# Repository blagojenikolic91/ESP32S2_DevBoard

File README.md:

# ESP32-S2-DevelopmentBoard

CUstom DIY Development board based around ESP32-S2, USB typeC, Native USB and fully addressable LED RGB build in. 

Features:

* ESP32-S2
* USB type C
* Fully addressable RGB LED 
* Native USB by default

## Revision 1.1.0

### Major Changes from rev 1.0.0

- BOM file (SMD resistance)
- PIN for RGB LED

### Minor Changes from rev 1.0.0

- PCB cutout for the Antena
- PIN Header for the Power (+3V3, 5V and GND)
- PIN description on the back side 

## Fabrication files 

Get fabrication files from [**Gumroad**](https://blnlabs.gumroad.com/l/ESP32-S2DevelopmentBoard) or clone project and create fabrication files by yourself with instryctions from 

* [**YouTube Video**: KiCad to JLCPCB - Gerber and SMD assembly](https://youtu.be/nr_URKTHS4Y)
* [**Blog Post**: Step-by-step guide: PCB from Schematic to Fabrication and Assembly](https://blnlabs.com/step-by-step-guide-pcb-from-schematic-to-fabrication-and-assembly/)

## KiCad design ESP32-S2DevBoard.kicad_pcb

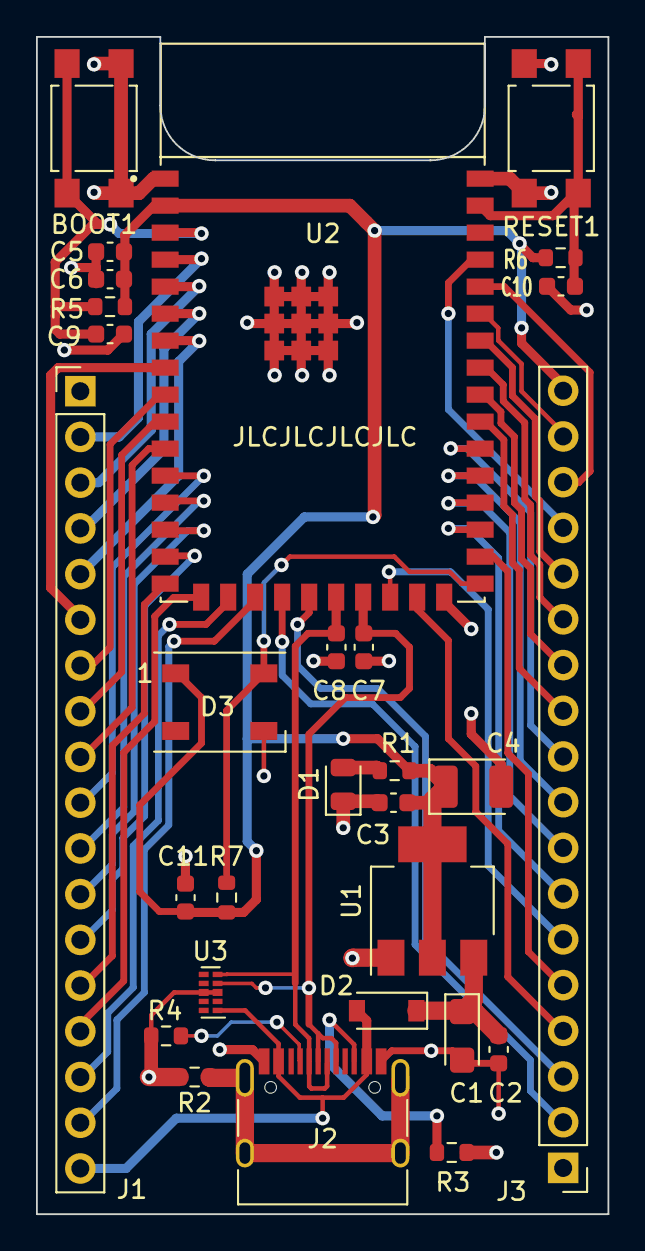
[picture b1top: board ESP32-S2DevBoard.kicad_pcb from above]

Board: 2 copper layers, 31.8 x 65.4 mm, 29 parts (0 on the bottom side), 45 nets.

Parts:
BOOT1: SW_SPST; SW_SPST_TL3305B
C1: 10uF; CP_EIA-3216-18_Kemet-A
C2, C3, C5: 100nF; C_0603_1608Metric
C4: 22uF; CP_EIA-3528-15_AVX-H
C6, C11: 10uF; C_0603_1608Metric
C7, C8: 22pF; C_0603_1608Metric
C9, C10: 1uF; C_0603_1608Metric
D1: Red LED; LED_0805_2012Metric
D2: D_Schottky; D_SOD-123
D3: WS2812B; LED_WS2812B_PLCC4_5.0x5.0mm_P3.2mm
J1, J3: Conn_01x18; PinHeader_1x18_P2.54mm_Vertical
J2: USB_C_Receptacle_USB2.0; USB_C_Receptacle_HRO_TYPE-C-31-M-12
R1, R3, R4: 5k1; R_0603_1608Metric
R2: 1M; R_0603_1608Metric
R5, R6, R7: 10k; R_0603_1608Metric
RESET1: SW_SPST; SW_SPST_TL3305B
U1: AMS1117-3.3; SOT-223-3_TabPin2
U2: ESP32-S2-WROOM; XCVR_ESP32-S2-WROOM
U3: TPD4E02B04DQA; USON-10_2.5x1.0mm_P0.5mm

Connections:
+3V3: C3.1, C4.1, C5.1, C6.1, C11.1, D3.1 (VDD), J3.18, R1.1, R5.1, R6.1, R7.1, U1.2 (VO), U2.2 (3V3)
+5V: D2.2 (A), J1.18, J2.A4 (VBUS), J2.A9 (VBUS), J2.B4 (VBUS), J2.B9 (VBUS), U3.1 (IO1)
Data+: C7.1, J2.A6 (D+), J2.B6 (D+), U2.23 (IO20), U3.4 (IO3)
Data-: C8.1, J2.A7 (D-), J2.B7 (D-), U2.22 (IO19), U3.5 (IO4)
Enable: C10.1, R6.2, RESET1.1 (A), U2.41 (EN)
GND: BOOT1.2 (B), C1.2, C2.2, C3.2, C4.2, C5.2, C6.2, C7.2, C8.2, C9.2, C10.2, C11.2, D1.1 (K), D3.3 (VSS), J1.1, J2.A1 (GND), J2.A12 (GND), J2.B1 (GND), J2.B12 (GND), J3.1, R2.2, R3.2, R4.2, RESET1.2 (B), U1.1 (GND), U2.1 (GND), U2.26 (GND), U2.42 (GND), U2.43 (GND), U2.44 (GND), U2.45 (GND), U2.46 (GND), U2.47 (GND), U2.48 (GND), U2.49 (GND), U2.50 (GND), U2.51 (GND), U3.3 (G), U3.8 (G)
GPIO0: BOOT1.1 (A), C9.1, R5.2, U2.3 (IO0)
GPIO1: J1.2, U2.4 (IO1)
GPIO2: J1.3, U2.5 (IO2)
GPIO3: J1.4, U2.6 (IO3)
GPIO4: J1.5, U2.7 (IO4)
GPIO5: J1.6, U2.8 (IO5)
GPIO6: J1.7, U2.9 (IO6)
GPIO7: J1.8, U2.10 (IO7)
GPIO8: J1.9, U2.11 (IO8)
GPIO9: J1.10, U2.12 (IO9)
GPIO10: J1.11, U2.13 (IO10)
GPIO11: J1.12, U2.14 (IO11)
GPIO12: J1.13, U2.15 (IO12)
GPIO13: J1.14, U2.16 (IO13)
GPIO14: J1.15, U2.17 (IO14)
GPIO15: J1.16, U2.18 (IO15)
GPIO16: J1.17, U2.19 (IO16)
GPIO17: J3.2, U2.20 (IO17)
GPIO18: J3.3, U2.21 (IO18)
GPIO21: J3.6, U2.24 (IO21)
GPIO26: J3.4, U2.25 (IO26)
GPIO34: J3.5, U2.28 (IO34)
GPIO35: J3.7, U2.29 (IO35)
GPIO36: J3.8, U2.30 (IO36)
GPIO37: J3.9, U2.31 (IO37)
GPIO38: J3.10, U2.32 (IO38)
GPIO39: J3.11, U2.33 (IO39)
GPIO40: J3.12, U2.34 (IO40)
GPIO41: J3.13, U2.35 (IO41)
GPIO42: J3.14, U2.36 (IO42)
GPIO45: J3.15, U2.39 (IO45)
unnamed: C1.1, C2.1, D2.1 (K), U1.3 (VI)
unnamed: D1.2 (A), R1.2
unnamed: J2.A5 (CC1), R4.1
unnamed: J2.B5 (CC2), R3.1
unnamed: J2.S1 (SHIELD), R2.1
RXDO: J3.16, U2.38 (RXD0)
StsLED: D3.4 (DIN), R7.2, U2.27 (IO33)
TXD0: J3.17, U2.37 (TXD0)

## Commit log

2023-02-09 Init commit for revision 1.1.0
